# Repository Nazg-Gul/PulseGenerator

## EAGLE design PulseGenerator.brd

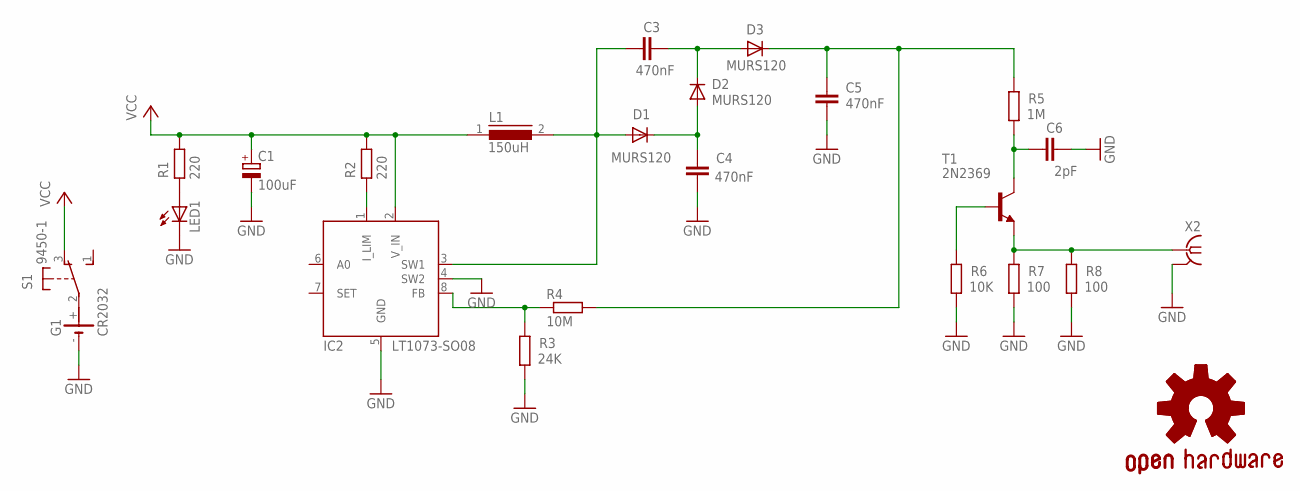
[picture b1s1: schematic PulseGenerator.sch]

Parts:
C1: 100uF; D/7343-31R
C3, C4, C5: 470nF; C1206
C6: 2pF; C1206
D1, D2, D3: MURS120; DO214AA
G1: CR2032; CR2032SMD
GOLD_ORB_SM1: OSHWLOGO_GOLD_ORB_SM; OSHW2
IC2: LT1073-SO08; SO08
L1: 150uH; DR125
LED1: LEDCHIPLED_1206; CHIPLED_1206
R1, R2: 220; R1206
R3: 24K; R1206
R4: 10M; R1206
R5: 1M; R1206
R6: 10K; R1206
R7, R8: 100; R1206
S1: 9450-1
T1: 2N2369; TO18
X2: BU-SMA-H

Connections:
GND: C1.-, C4.2, C5.2, C6.1, G1.-, IC2.4 (SW2), IC2.5 (GND), LED1.C, R3.1, R6.1, R7.1, R8.1, X2.2 (GND), X2.3 (GND), X2.4 (GND), X2.5 (GND)
unnamed: C4.1, D1.C, D2.A
unnamed: LED1.A, R1.1
unnamed: G1.+, S1.2
unnamed: C3.1, D2.C, D3.A
unnamed: IC2.1 (I_LIM), R2.1
unnamed: C6.2, R5.1, T1.3 (C)
unnamed: C5.1, D3.C, R4.2, R5.2
unnamed: C3.2, D1.A, IC2.3 (SW1), L1.2
unnamed: IC2.8 (FB), R3.2, R4.1
unnamed: R6.2, T1.2 (B)
unnamed: R7.2, R8.2, T1.1 (E), X2.1
VCC: C1.+, IC2.2 (V_IN), L1.1, R1.2, R2.2, S1.3 (O)

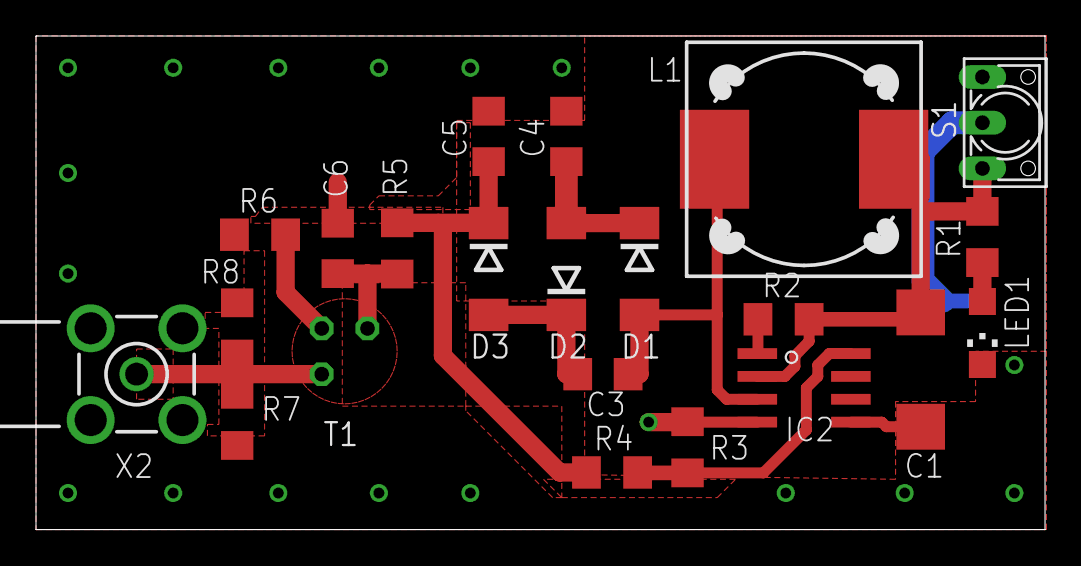
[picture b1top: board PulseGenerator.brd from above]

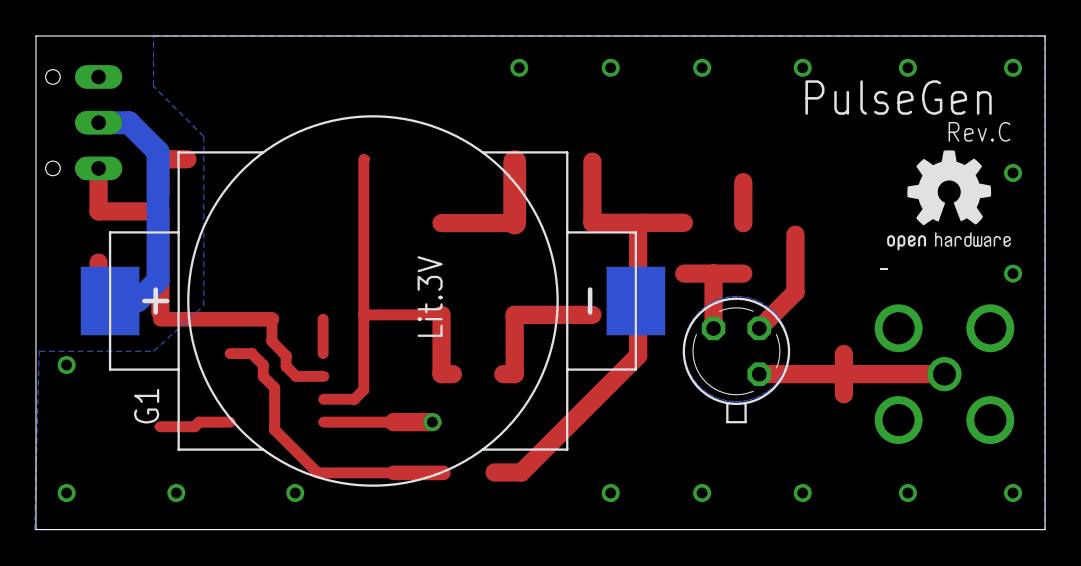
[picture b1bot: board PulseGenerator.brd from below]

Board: 2 copper layers, 56.1 x 27.4 mm, 24 parts (3 on the bottom side), 13 nets.

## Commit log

2017-01-21 Initial commit of Rev.B
2017-01-21 Commit of the current version
